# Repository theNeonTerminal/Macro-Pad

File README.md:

# BLE Macro Pad

### ESP32 wireless macro pad with 12 customizable buttons, a rotary encoder, and an OLED

**12 configurable macro actions · Rotary volume control · OLED feedback · Bluetooth LE**

*A small DIY shortcut pad for media controls and everyday keyboard macros.*

---

## About

An ESP32 based BLE Macro Pad I made as a project to experiment with BLE on the ESP32 and simulate keyboard/mouse (mouse not used here) actions wirelessly via BLE.

Each button on the pad has its own function dedicated to make any required action on the pc or the phone its connected to.

> [!IMPORTANT]
> **Arduino IDE ESP32 board package: version `2.0.17`.** Use **ESP32 by Espressif Systems v2.0.17** for this project. The current firmware does **not compile with newer core versions** due to changes made to the Bluetooth API by Espressif.

## Hardware Design

### 01 / Circuit Schematic

<div align="center">

</div>

### 02 / PCB Layout

<div align="center">

</div>

### 03 / PCB 3D View

<div align="center">

</div>

## Currently Implemented Features

- **Bluetooth LE keyboard:** Send keystrokes wirelessly, while also consuming very amount of battery.
- **Customizable macros:** Dedicated `b1()`–`b12()` functions make actions easy to edit and customize to ones needs and wishes
- **Rotary encoder:** To adjust connected system volume.
- **OLED feedback:** Show the last triggered action on a 128x64 I2C OLED Display - can be customized to show animations, gifs (in monochrome) and really anything.
- **Expandable firmware:** Some of the buttons remains unused as of today, so it allows it to have some space for more functionality.

---

## BoM (Bill of Materials)

| PART | QUANTITY | PURPOSE |
| ----- | --- | ---- |
| ESP32 | 1 | Main BLE control unit and processing unit |
| OLED Display | 1 | Dsiplay currently transmited signal or any other stat (customizable) |
| Rotary Encoder | 1 | To adjust volume of the connected device |
| Mechanical Switches | 12 | The actual input for the macros itself |
| Mechanical Switch Keycaps | 12 | To put on the mechanical switches |
| PCB | 1 | To house and connect all electronics |
| TP4056 Charging Module | 1 | To charge the onboard battery |
| Battery (Li-Ion any mAh) | 1 | To Power the system |
| Slide switch | 1 | To turn the system on or off |

---

## Button Layout

The schematic uses 12 independent pushbuttons. Each button connects between its GPIO and GND and is read with `INPUT_PULLUP`.

| Button | GPIO (PCB schematic) | Default firmware action |
| :--- | :--- | :--- |
| SW1 | GPIO 13 | Up arrow |
| SW2 | GPIO 25 | Down arrow |
| SW3 | GPIO 36 (VP) | Left arrow |
| SW4 | GPIO 12 | Right arrow |
| SW5 | GPIO 39 (VN) | Space |
| SW6 | GPIO 26 | Next track |
| SW7 | GPIO 34 | Previous track |
| SW8 | GPIO 14 | Play / pause |
| SW9 | GPIO 33 | Custom |
| SW10 | GPIO 35 | Custom |
| SW11 | GPIO 15 | Custom |
| SW12 | GPIO 18 | Custom |

**Other connections:** The OLED uses I²C; the rotary encoder is intended for volume control. Refer to the schematic for their PCB connections.

## Firmware Working

This code uses the <a href="https://github.com/T-vK/ESP32-BLE-Keyboard">BLEKeyboard</a> libray - detects button presses with a function that I found online, the function returns `true` immediately when a button is pressed and periodically sends `true` (300ms) if the button is not released at all, very helpful function, cant really tell how it works, but it works great and is fully non-blocking. The main code starts only the BLEKeyboard is connected to a device (name, manufaturer and charge can be configured the object instance outside and above the setup function), the code simply checks for button presses (form the switch case part) and calls the button function associated with the button and same with rotary encoder - checks the reading, manages an internal counter and send BLE signal

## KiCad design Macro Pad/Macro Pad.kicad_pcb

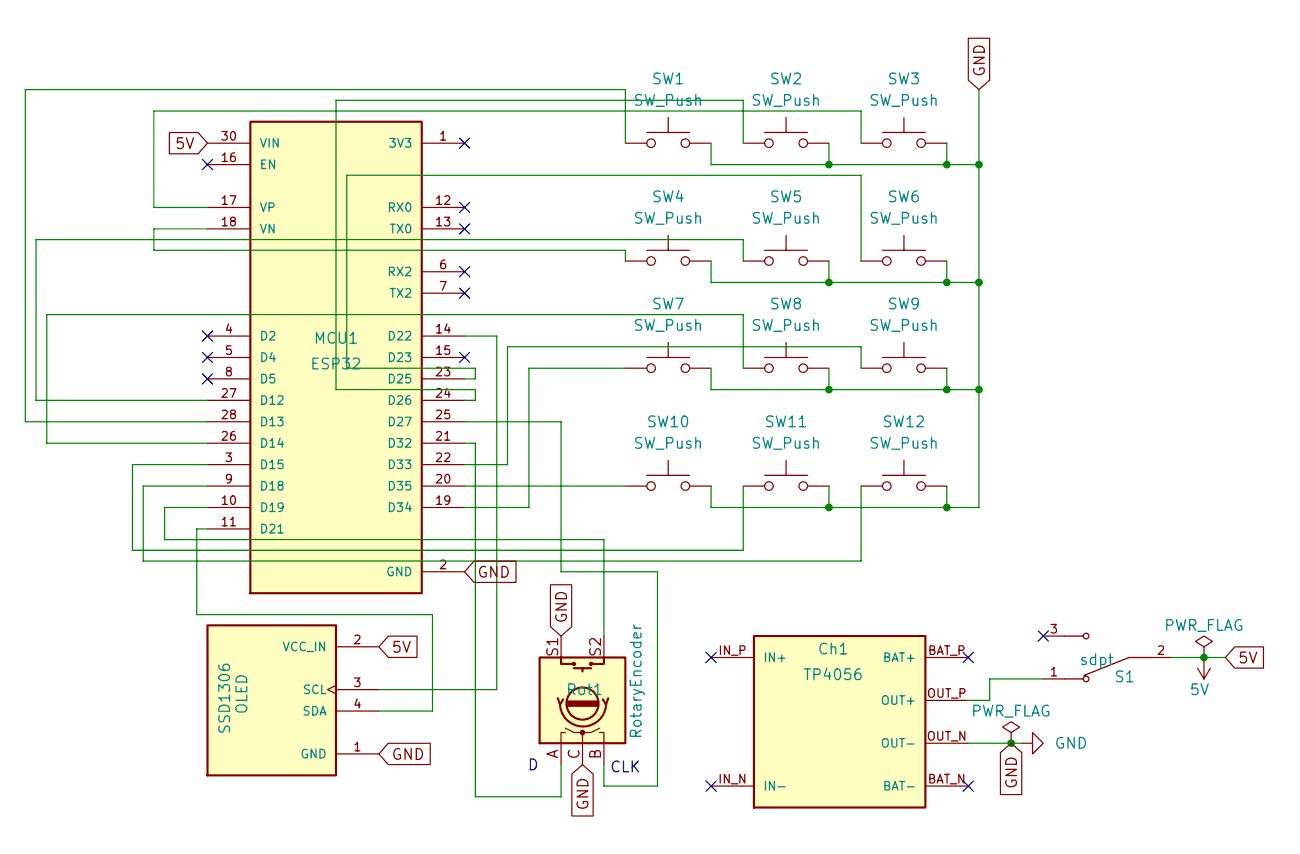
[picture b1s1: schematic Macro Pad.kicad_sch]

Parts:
Ch1: TP4056; MODULE_TP4056_MICRO-USB_CHARGER_-_1A
MCU1: ESP32; ESP32-30-pin
OLED: SSD1306; OLED-SSD1306; PARTREV 2018-09-10
Rot1: RotaryEncoder; RotaryEncoder_Alps_EC11E-Switch_Vertical_H20mm
S1: sdpt; SW_ATE1D-2M3-10-Z; PARTREV N/A
SW1, SW2, SW3, SW4, SW5, SW6, SW7, SW8, SW9, SW10, SW11, SW12: SW_Push; SW_Cherry_MX_PCB_1.00u

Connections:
5V: MCU1.30 (VIN), OLED.2 (VCC_IN), S1.2; also elsewhere on the board
GND: Ch1.OUT_N (OUT-), MCU1.2 (GND), MCU1.29 (GND), OLED.1 (GND), Rot1.C, Rot1.S1, SW1.2, SW2.2, SW3.2, SW4.2, SW5.2, SW6.2, SW7.2, SW8.2, SW9.2, SW10.2, SW11.2, SW12.2; also elsewhere on the board
unnamed: Ch1.OUT_P (OUT+), S1.1
unnamed: MCU1.27 (D12), SW5.1
unnamed: MCU1.28 (D13), SW1.1
unnamed: MCU1.26 (D14), SW8.1
unnamed: MCU1.3 (D15), SW11.1
unnamed: MCU1.9 (D18), SW12.1
unnamed: MCU1.10 (D19), Rot1.S2
unnamed 9: MCU1.11 (D21), OLED.4 (SDA); also elsewhere on the board
unnamed 10: MCU1.14 (D22), OLED.3 (SCL); also elsewhere on the board
unnamed: MCU1.23 (D25), SW6.1
unnamed: MCU1.24 (D26), SW2.1
unnamed: MCU1.25 (D27), Rot1.B
unnamed: MCU1.21 (D32), Rot1.A
unnamed: MCU1.22 (D33), SW9.1
unnamed: MCU1.19 (D34), SW7.1
unnamed: MCU1.20 (D35), SW10.1
unnamed: MCU1.18 (VN), SW4.1
unnamed: MCU1.17 (VP), SW3.1

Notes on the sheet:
CLK

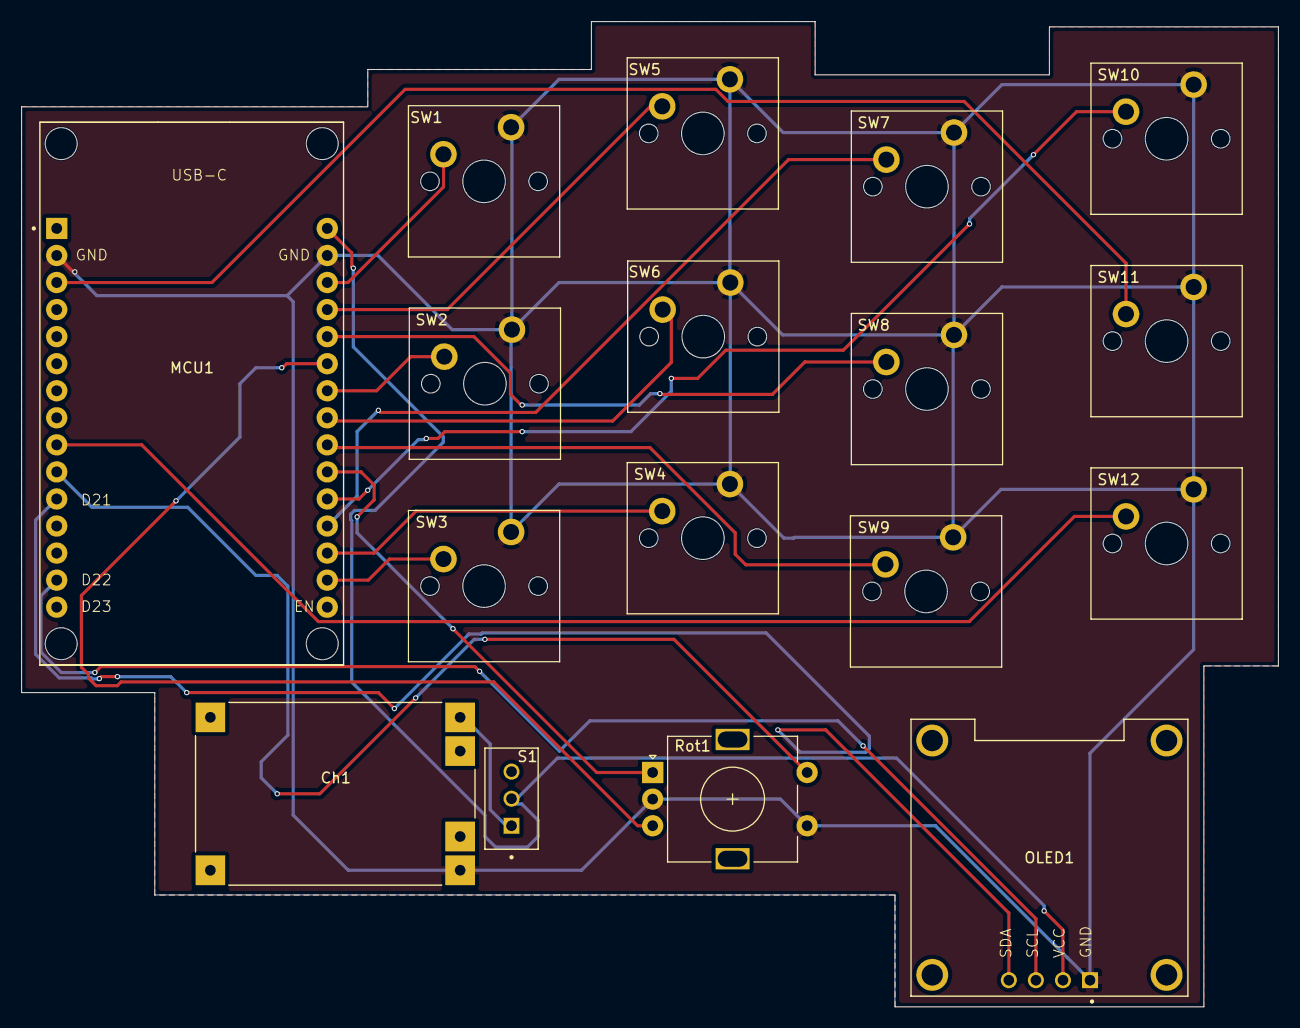
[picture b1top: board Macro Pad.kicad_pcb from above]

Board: 2 copper layers, 118.0 x 92.5 mm, 17 parts (0 on the bottom side), 20 nets.

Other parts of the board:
OLED1: SSD1306; OLED-SSD1306

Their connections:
5V: OLED1.2 (VCC_IN); also elsewhere on the board
GND: OLED1.1 (GND); also elsewhere on the board
unnamed 9: OLED1.4 (SDA); also elsewhere on the board
unnamed 10: OLED1.3 (SCL); also elsewhere on the board

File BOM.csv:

"Reference","Qty","Value","DNP","Exclude from BOM","Exclude from Board","Exclude from Simulation","Exclude from Position Files","Footprint","Datasheet"
"Ch1","1","TP4056","","","","","${EXCLUDE_FROM_POS_FILES}","TP4056:MODULE_TP4056_MICRO-USB_CHARGER_-_1A",""
"MCU1","1","ESP32","","","","","${EXCLUDE_FROM_POS_FILES}","ESP32 30 pin:ESP32-30-pin",""
"OLED1","1","SSD1306","","","","","${EXCLUDE_FROM_POS_FILES}","OLED SSD1306:OLED-SSD1306",""
"Rot1","1","RotaryEncoder","","","","","${EXCLUDE_FROM_POS_FILES}","Rotary_Encoder:RotaryEncoder_Alps_EC11E-Switch_Vertical_H20mm",""
"S1","1","sdpt","","","","","${EXCLUDE_FROM_POS_FILES}","spdt:SW_ATE1D-2M3-10-Z",""
"SW1,SW2,SW3,SW4,SW5,SW6,SW7,SW8,SW9,SW10,SW11,SW12","12","SW_Push","","","","","${EXCLUDE_FROM_POS_FILES}","PCM_Switch_Keyboard_Cherry_MX:SW_Cherry_MX_PCB_1.00u",""
